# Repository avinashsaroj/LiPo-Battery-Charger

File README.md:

# LiPo-Battery-Charger
KiCAD
# Lithium Polymer battery cahrger

A single LiPo battery charger using Microchip's MCP73831/2.

## Components

1. MCP73831/2
2. Micro USB
3. LiPo battery female header
4. LED for charge indication

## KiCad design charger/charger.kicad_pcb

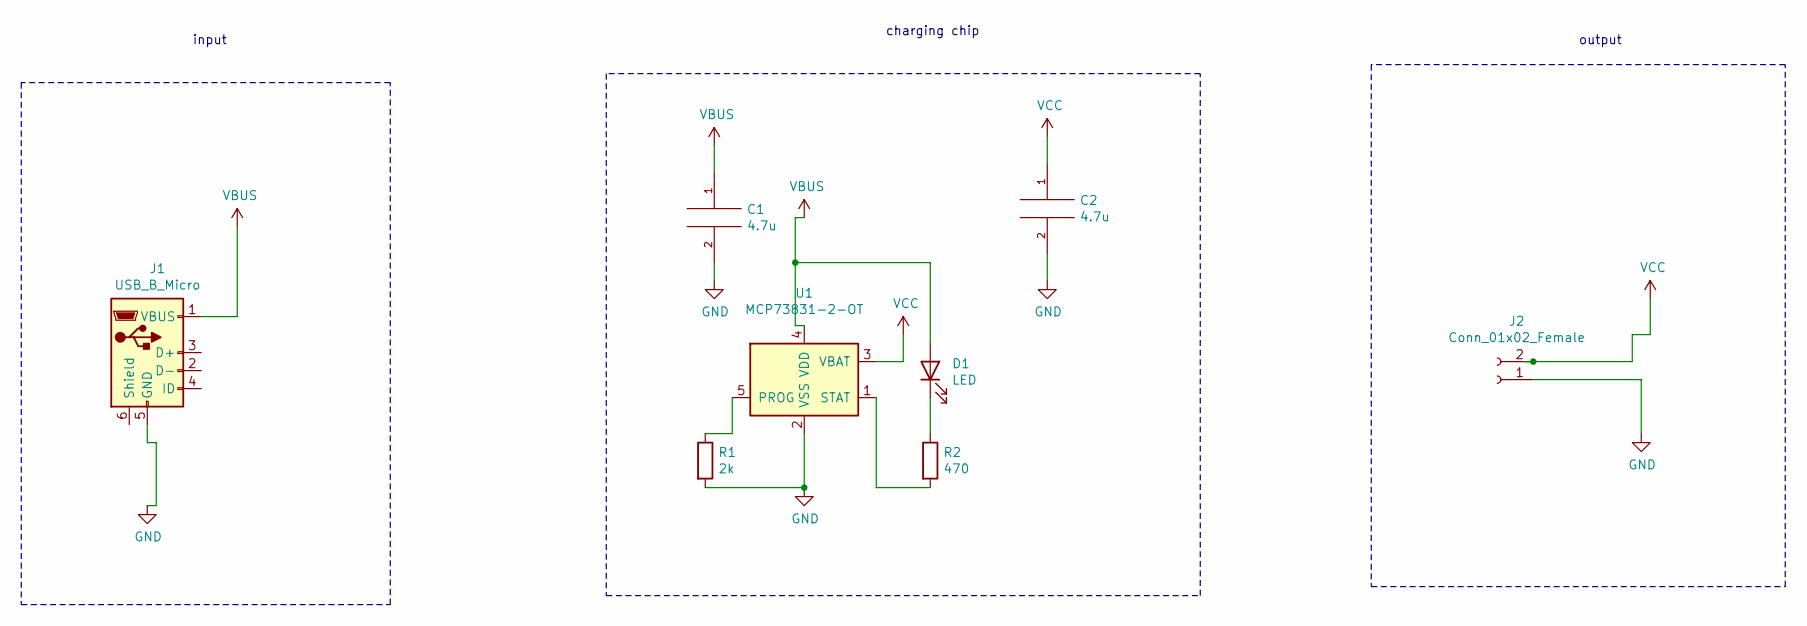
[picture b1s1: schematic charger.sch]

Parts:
C1, C2: 4.7u; C_1206_3216Metric_Pad1.33x1.80mm_HandSolder
D1: LED; LED_1206_3216Metric_Pad1.42x1.75mm_HandSolder
J1: USB_B_Micro; USB_Micro-B_Molex-105017-0001
J2: Conn_01x02_Female; JST_PH_B2B-PH-K_1x02_P2.00mm_Vertical
R1: 2k; R_2512_6332Metric_Pad1.40x3.35mm_HandSolder
R2: 470; R_2512_6332Metric_Pad1.40x3.35mm_HandSolder
U1: MCP73831-2-OT; SOT-23-5

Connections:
GND: C1.2, C2.2, J1.5 (GND), J2.1, R1.2, U1.2 (VSS)
unnamed: D1.1 (K), R2.1
unnamed: R1.1, U1.5 (PROG)
unnamed: R2.2, U1.1 (STAT)
VBUS: C1.1, D1.2 (A), J1.1 (VBUS), U1.4 (VDD)
VCC: C2.1, J2.2, U1.3 (VBAT)

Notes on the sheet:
input
charging chip
output

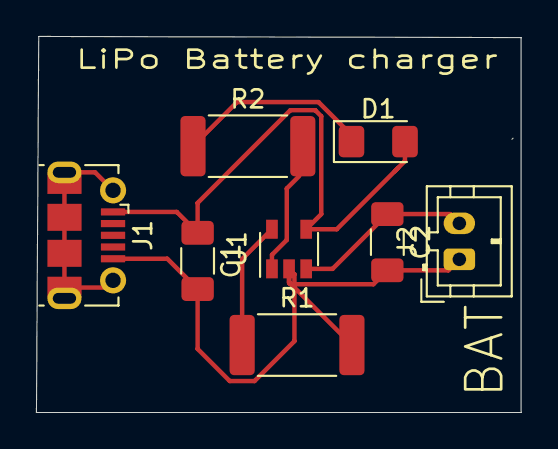
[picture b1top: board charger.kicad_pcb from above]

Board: 2 copper layers, 26.9 x 20.9 mm, 8 parts (0 on the bottom side), 6 nets.
